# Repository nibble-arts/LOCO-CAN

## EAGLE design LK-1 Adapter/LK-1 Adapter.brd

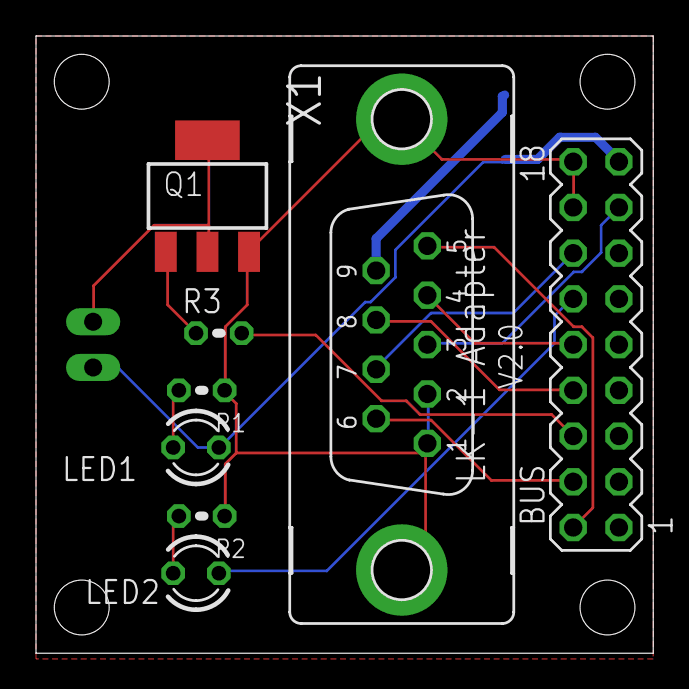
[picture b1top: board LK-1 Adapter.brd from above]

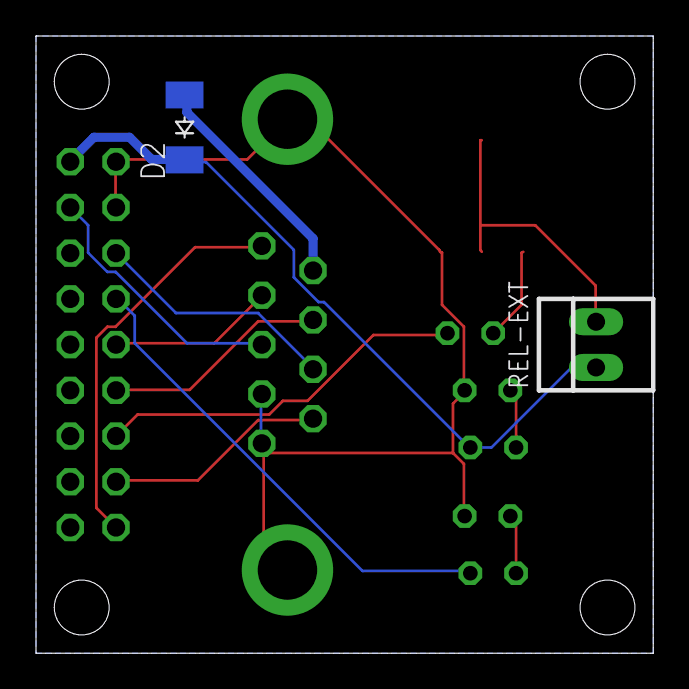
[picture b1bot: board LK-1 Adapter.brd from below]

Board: 2 copper layers, 34.3 x 34.3 mm, 10 parts (2 on the bottom side), 15 nets.

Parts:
BUS: MA09-2
D2: CGRM4004-G; SOD-123_MINI-SMA
LED1, LED2: LED3MM
Q1: N-HEXFET-2D_SOT232-; SOT223
R1: 1K; 0204V
R2: 330R; 0204V
R3: 10K; 0204V
REL-EXT: 22-23-2021
X1: F09VP

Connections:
+12V: BUS.17, D2.C, LED1.A, REL-EXT.1
D2: BUS.2, X1.5
D3: BUS.4, X1.6
D4: BUS.6, R3.2
D5: BUS.8, X1.8
D6: BUS.10, X1.4
D7: BUS.12, LED2.A
D8: BUS.14, X1.7
D9: BUS.15, X1.3
GND: BUS.16, BUS.18, Q1.3, R1.1, R2.1, X1.1, X1.2, X1.G1, X1.G2
unnamed: Q1.1, R3.1
unnamed: Q1.2, Q1.4, REL-EXT.2
unnamed: D2.A, X1.9
unnamed: LED1.K, R1.2
unnamed: LED2.K, R2.2

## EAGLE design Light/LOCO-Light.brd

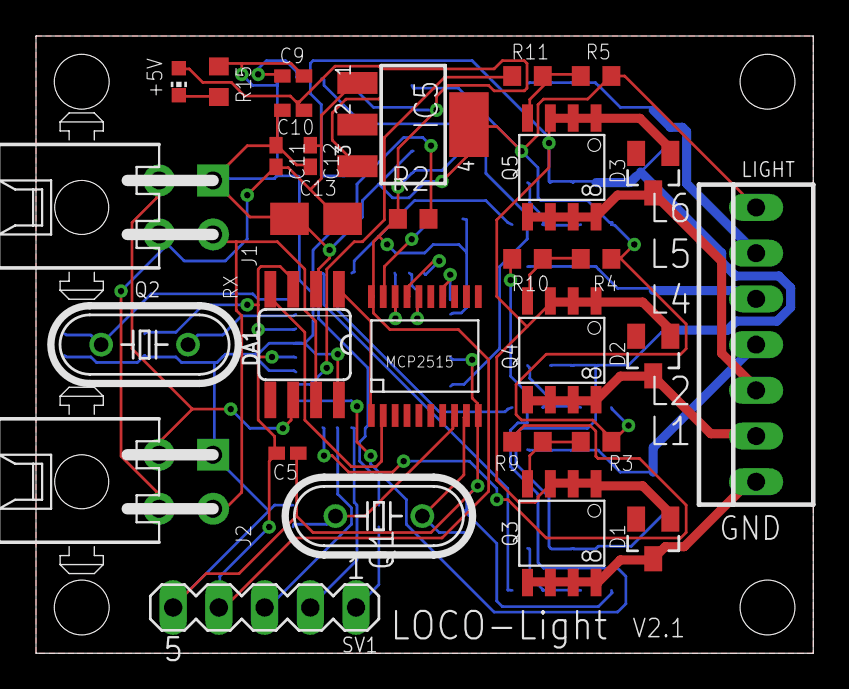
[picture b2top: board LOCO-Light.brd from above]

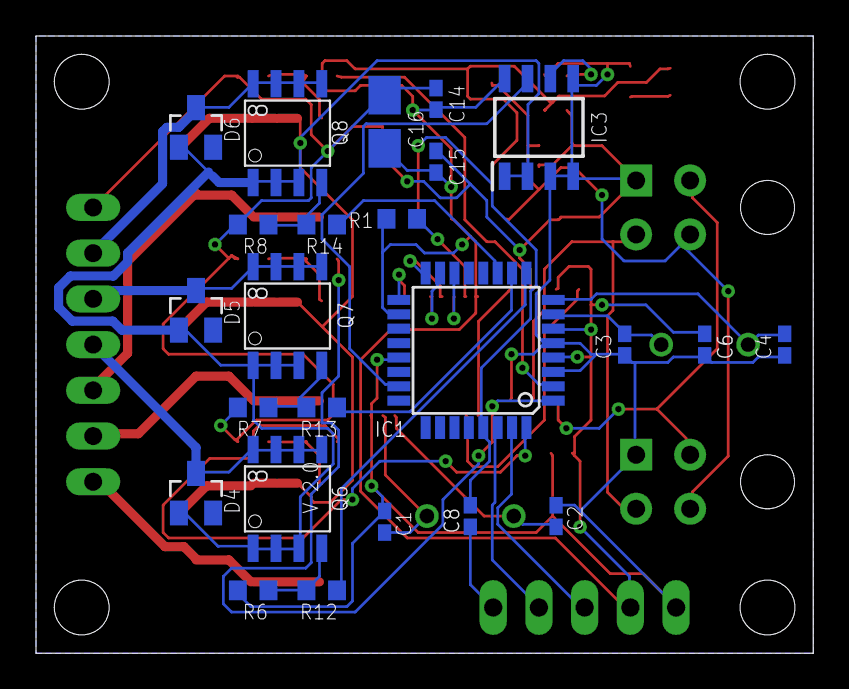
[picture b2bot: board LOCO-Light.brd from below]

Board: 2 copper layers, 43.2 x 34.3 mm, 54 parts (24 on the bottom side), 42 nets.

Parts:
+5V: CHIP-LED0603
C1, C2, C3, C4: 22p; C0402K
C5, C6, C8, C10, C11, C15: 100n; C0402K
C9, C12, C14: 1n; C0402K
C13, C16: 16uF; A/3216-18W
D1, D2, D3, D4, D5, D6: BAS40; SOT23
DA1: TJA1050; SO08
IC1: Atmega 328-P; TQFP32-08
IC2: MCP2515; TSSOP20
IC3: ACS712ELCTR-20A-T; SOIC127P600X175-8N
IC5: LM340MP-05; SOT223
J1, J2: 3-794618-4; SHDRRA4W102P300_2X2_686X892X73
LIGHT: 22-23-2071
Q1: 8MHz; HC49/S
Q2: 16MHz; HC49/S
Q3, Q4, Q5, Q6, Q7, Q8: FDS5680; SO-8
R1, R2, R3, R4, R5, R6, R7, R8, R9, R10, R11, R12, R13, R14, R15: 10k; R0603
SV1: MA05-1

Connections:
+12V: C11.2, C12.2, C13.+, IC5.1, J1.4, J2.4
A0: IC1.23, IC3.7
CAN-H: DA1.7, J1.3, J2.3
CAN-L: DA1.6, J1.2, J2.2
CAN-OCC1: C1.1, IC2.9, Q1.1
CAN-OCC2: C2.1, IC2.8, Q1.2
CS: IC1.14, IC2.18
D2: IC1.32, R9.2
D3: IC1.1, R10.2
D4: IC1.2, R11.2
D5: IC1.9, R12.2
D6: IC1.10, R13.2
D7: IC1.11, R14.2
DTR: C8.1, SV1.1
GND: C1.2, C2.2, C3.2, C4.2, C5.1, C6.2, C9.1, C10.1, C11.1, C12.1, C13.-, C14.1, C15.1, C16.-, DA1.2, DA1.8, IC1.3, IC1.5, IC1.21, IC2.10, IC3.3, IC3.4, IC3.5, IC5.4, J1.1, J2.1, LIGHT.7, R3.1, R4.1, R5.1, R6.1, R7.1, R8.1, R15.1, SV1.5
L1: D1.3, LIGHT.1, Q3.5, Q3.6, Q3.7, Q3.8
L2: D2.3, LIGHT.2, Q4.5, Q4.6, Q4.7, Q4.8
L3: D3.3, LIGHT.3, Q5.5, Q5.6, Q5.7, Q5.8
L4: D4.3, LIGHT.4, Q6.5, Q6.6, Q6.7, Q6.8
L5: D5.3, LIGHT.5, Q7.5, Q7.6, Q7.7, Q7.8
L6: D6.3, LIGHT.6, Q8.5, Q8.6, Q8.7, Q8.8
LIGHT-GND: D1.1, D2.1, D3.1, D4.1, D5.1, D6.1, IC3.1, IC3.2, Q3.1, Q3.2, Q3.3, Q4.1, Q4.2, Q4.3, Q5.1, Q5.2, Q5.3, Q6.1, Q6.2, Q6.3, Q7.1, Q7.2, Q7.3, Q8.1, Q8.2, Q8.3
unnamed: C9.2, IC3.6
unnamed: Q3.4, R3.2, R9.1
unnamed: Q4.4, R4.2, R10.1
unnamed: Q5.4, R5.2, R11.1
unnamed: Q6.4, R6.2, R12.1
unnamed: IC2.19, R1.1
unnamed: Q7.4, R7.2, R13.1
unnamed: Q8.4, R8.2, R14.1
unnamed: C3.1, IC1.7, Q2.1
unnamed: C4.1, IC1.8, Q2.2
unnamed: +5V.C, R15.2
unnamed: C8.2, IC1.29, R2.1
RX: IC1.31, SV1.3
RXCAN: DA1.4, IC2.2
SCK: IC1.17, IC2.14
SI: IC1.16, IC2.17
SO: IC1.15, IC2.16
TX: IC1.30, SV1.2
TXCAN: DA1.1, IC2.1
VCC: +5V.A, C5.2, C6.1, C10.2, C14.2, C15.2, C16.+, DA1.3, IC1.4, IC1.6, IC1.18, IC2.20, IC3.8, IC5.3, R1.2, R2.2, SV1.4

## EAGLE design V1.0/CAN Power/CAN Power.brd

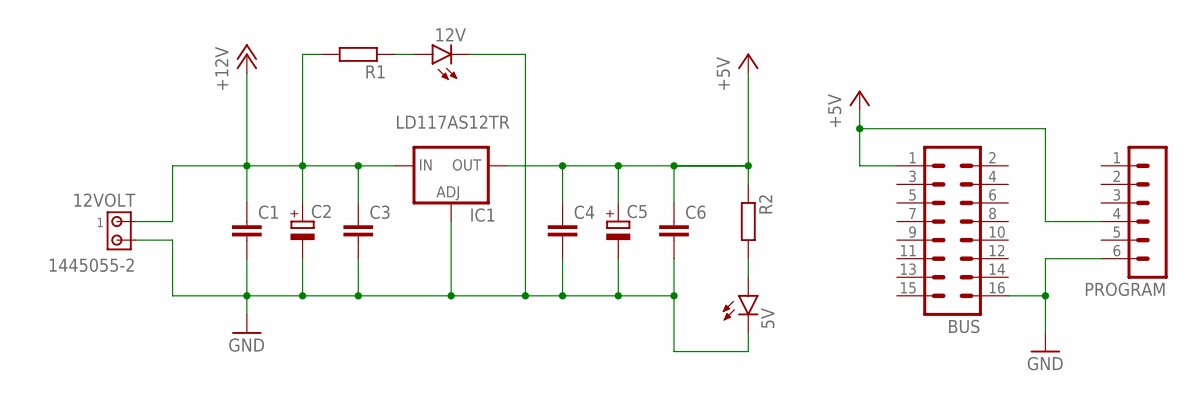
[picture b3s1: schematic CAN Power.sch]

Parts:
5V, 12V: LED3MM
12VOLT: 1445055-2
BUS: MA08-2
C1, C3, C4, C6: C-EUC0402; C0402
C2, C5: CPOL-EUC/6032-28R; C/6032-28R
IC1: LD117AS12TR; SOT223
PROGRAM: MA06-1
R1, R2: R-EU_R0402; R0402

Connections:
+5V: BUS.1, C4.1, C5.+, C6.1, IC1.4 (OUT), PROGRAM.4, R2.1
+12V: 12VOLT.1, C1.1, C2.+, C3.1, IC1.3 (IN), R1.2
GND: 5V.K (C), 12V.K (C), 12VOLT.2, BUS.16, C1.2, C2.-, C3.2, C4.2, C5.-, C6.2, IC1.1 (ADJ), PROGRAM.6
unnamed: 5V.A, R2.2
unnamed: 12V.A, R1.1

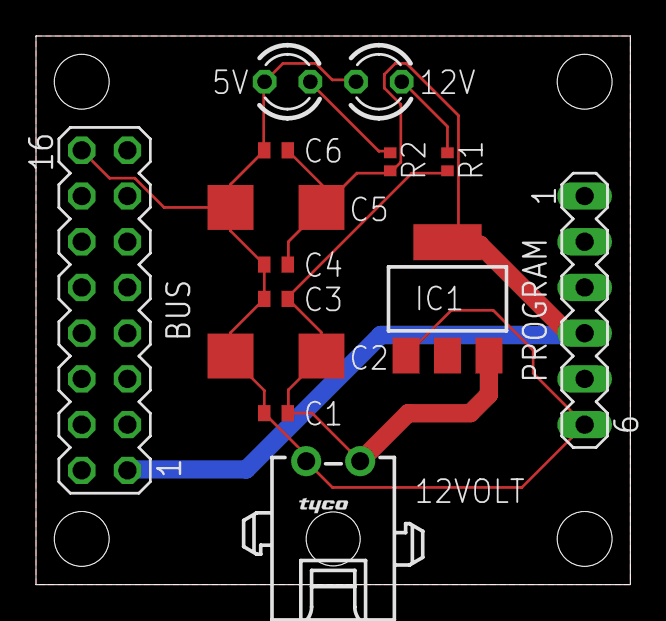
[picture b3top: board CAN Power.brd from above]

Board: 2 copper layers, 33.0 x 30.5 mm, 14 parts (0 on the bottom side), 5 nets.

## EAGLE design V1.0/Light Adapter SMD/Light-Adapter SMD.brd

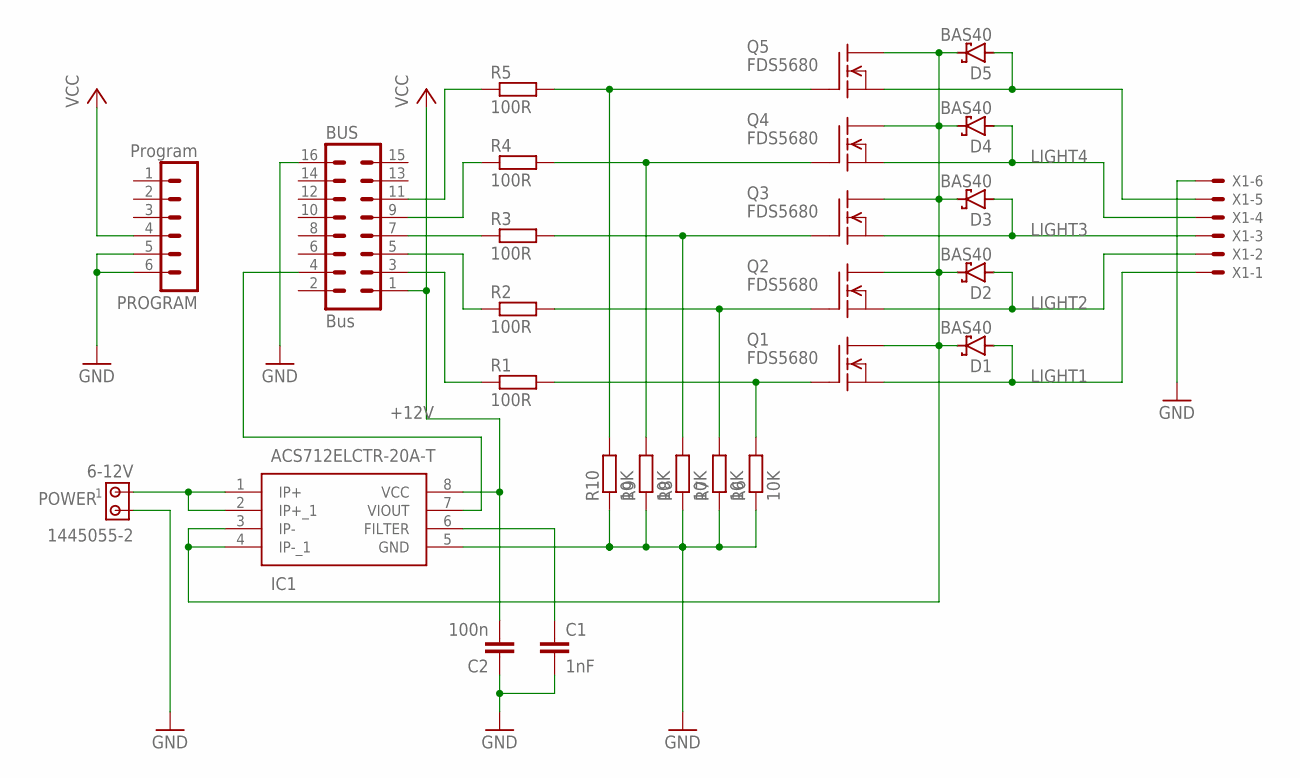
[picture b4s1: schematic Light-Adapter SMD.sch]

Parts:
6-12V: 1445055-2
BUS: Bus; MA08-2
C1: 1nF; C0402
C2: 100n; C0402
D1, D2, D3, D4, D5: BAS40; SOT23
IC1: ACS712ELCTR-20A-T; SOIC127P600X175-8N
PROGRAM: Program; MA06-1
Q1, Q2, Q3, Q4, Q5: FDS5680; SO-8
R1, R2, R3, R4, R5: 100R; R0402
R6, R7, R8, R9, R10: 10K; R0402
X1: 22-23-2061

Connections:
+12V: D1.3 (C), D2.3 (C), D3.3 (C), D4.3 (C), D5.3 (C), IC1.3 (IP-), IC1.4 (IP-_1), Q1.5 (D), Q1.6 (D), Q1.7 (D), Q1.8 (D), Q2.5 (D), Q2.6 (D), Q2.7 (D), Q2.8 (D), Q3.5 (D), Q3.6 (D), Q3.7 (D), Q3.8 (D), Q4.5 (D), Q4.6 (D), Q4.7 (D), Q4.8 (D), Q5.5 (D), Q5.6 (D), Q5.7 (D), Q5.8 (D)
GND: 6-12V.2, BUS.16, C1.2, C2.1, IC1.5 (GND), PROGRAM.5, PROGRAM.6, R6.1, R7.1, R8.1, R9.1, R10.1, X1.6
LIGHT1: D1.1 (A), Q1.1 (S), Q1.2 (S), Q1.3 (S), X1.1
LIGHT2: D2.1 (A), Q2.1 (S), Q2.2 (S), Q2.3 (S), X1.2
LIGHT3: D3.1 (A), Q3.1 (S), Q3.2 (S), Q3.3 (S), X1.3
LIGHT4: D4.1 (A), Q4.1 (S), Q4.2 (S), Q4.3 (S), X1.4
LIGHT5: D5.1 (A), Q5.1 (S), Q5.2 (S), Q5.3 (S), X1.5
unnamed: BUS.3, R1.1
unnamed: BUS.5, R2.1
unnamed: BUS.7, R3.1
unnamed: BUS.9, R4.1
unnamed: BUS.4, IC1.7 (VIOUT)
unnamed: C1.1, IC1.6 (FILTER)
unnamed: BUS.11, R5.1
unnamed: Q5.4 (G), R5.2, R10.2
unnamed: Q4.4 (G), R4.2, R9.2
unnamed: Q3.4 (G), R3.2, R8.2
unnamed: Q2.4 (G), R2.2, R7.2
unnamed: Q1.4 (G), R1.2, R6.2
POWER: 6-12V.1, IC1.1 (IP+), IC1.2 (IP+_1)
VCC: BUS.1, C2.2, IC1.8 (VCC), PROGRAM.4

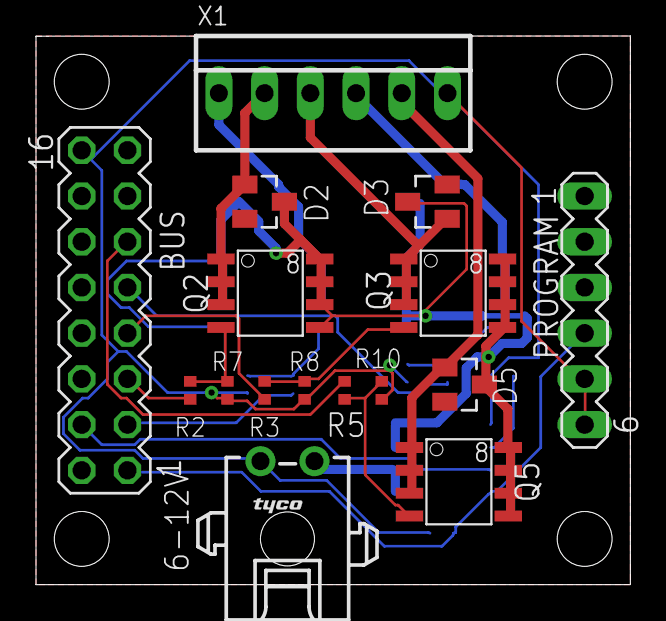
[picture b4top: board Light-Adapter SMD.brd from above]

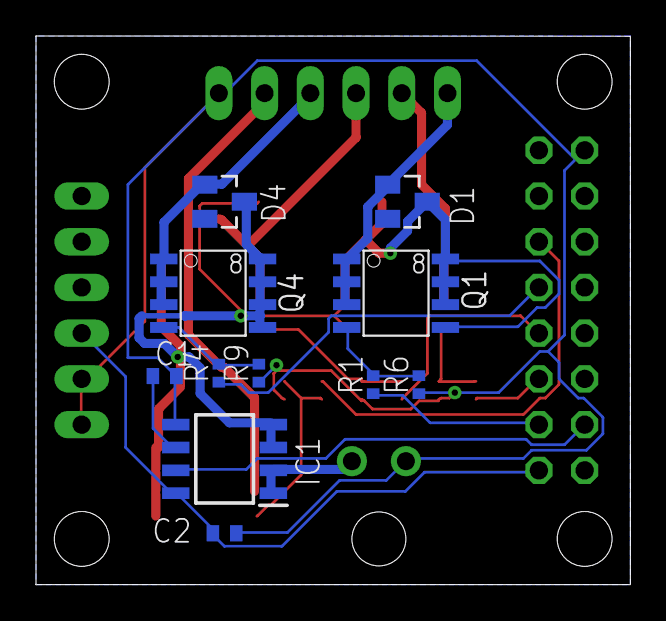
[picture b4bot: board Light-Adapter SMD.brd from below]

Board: 2 copper layers, 33.0 x 30.5 mm, 27 parts (11 on the bottom side), 21 nets.

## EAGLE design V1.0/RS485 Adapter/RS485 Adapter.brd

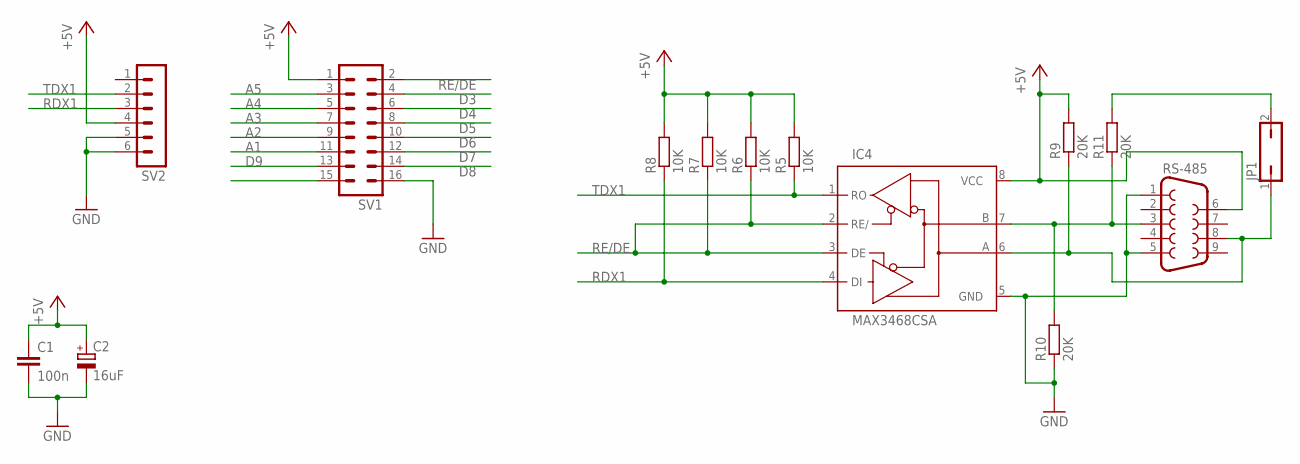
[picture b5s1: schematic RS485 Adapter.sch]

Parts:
C1: 100n; C0402
C2: 16uF; A/3216-18R
IC4: MAX3468CSA; SO08
JP1: JP1Q; JP1
R5, R6, R7, R8: 10K; MINI_MELF-0102R
R9, R10, R11: 20K; MINI_MELF-0102R
RS-485: F09V
SV1: MA08-2
SV2: MA06-1

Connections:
+5V: C1.1, C2.+, IC4.8 (VCC), R5.2, R6.2, R7.2, R8.2, R9.2, RS-485.6, SV1.1, SV2.4
A1: SV1.11
A2: SV1.9
A3: SV1.7
A4: SV1.5
A5: SV1.3
D3: SV1.4
D4: SV1.6
D5: SV1.8
D6: SV1.10
D7: SV1.12
D8: SV1.14
D9: SV1.13
GND: C1.2, C2.-, IC4.5 (GND), R10.1, RS-485.1, RS-485.5, SV1.16, SV2.5, SV2.6
IO14: SV1.15
unnamed: IC4.6 (A), JP1.1, R9.1, RS-485.8
unnamed: IC4.7 (B), R10.2, R11.1, RS-485.3
unnamed: JP1.2, R11.2
RDX1: IC4.4 (DI), R8.1, SV2.3
RE/DE: IC4.2 (RE/), IC4.3 (DE), R6.1, R7.1, SV1.2
TDX1: IC4.1 (RO), R5.1, SV2.2

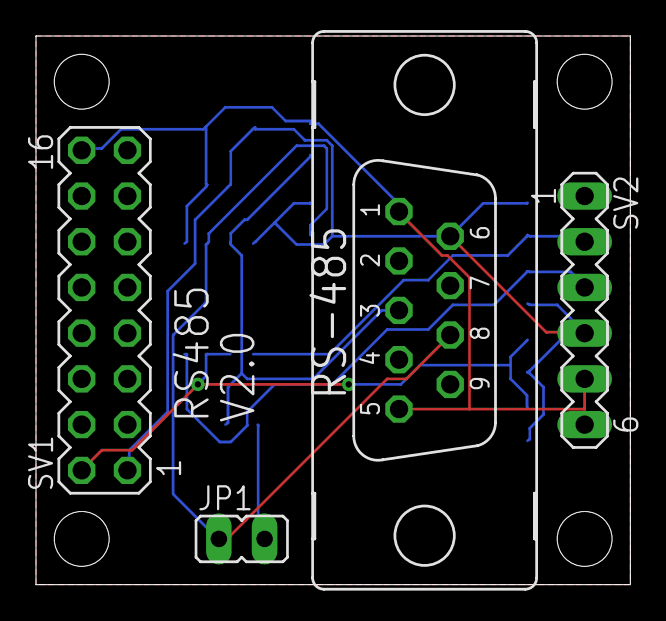
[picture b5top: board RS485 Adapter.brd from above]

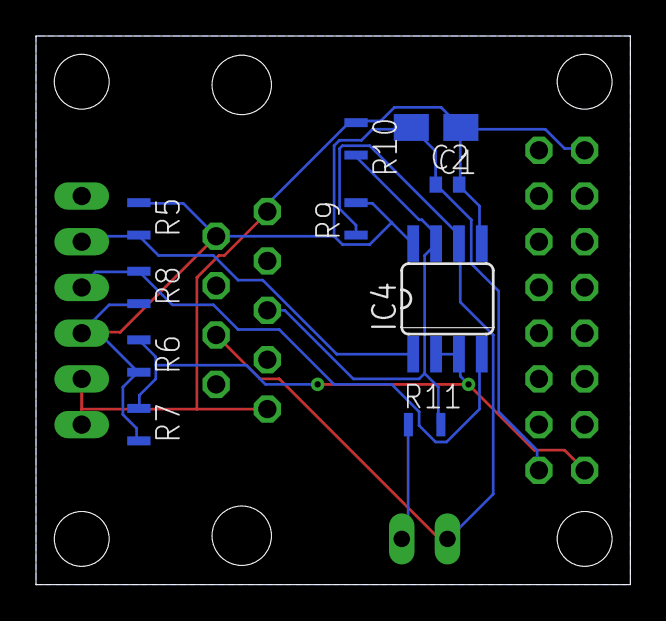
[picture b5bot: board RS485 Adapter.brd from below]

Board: 2 copper layers, 33.0 x 30.5 mm, 14 parts (10 on the bottom side), 8 nets.

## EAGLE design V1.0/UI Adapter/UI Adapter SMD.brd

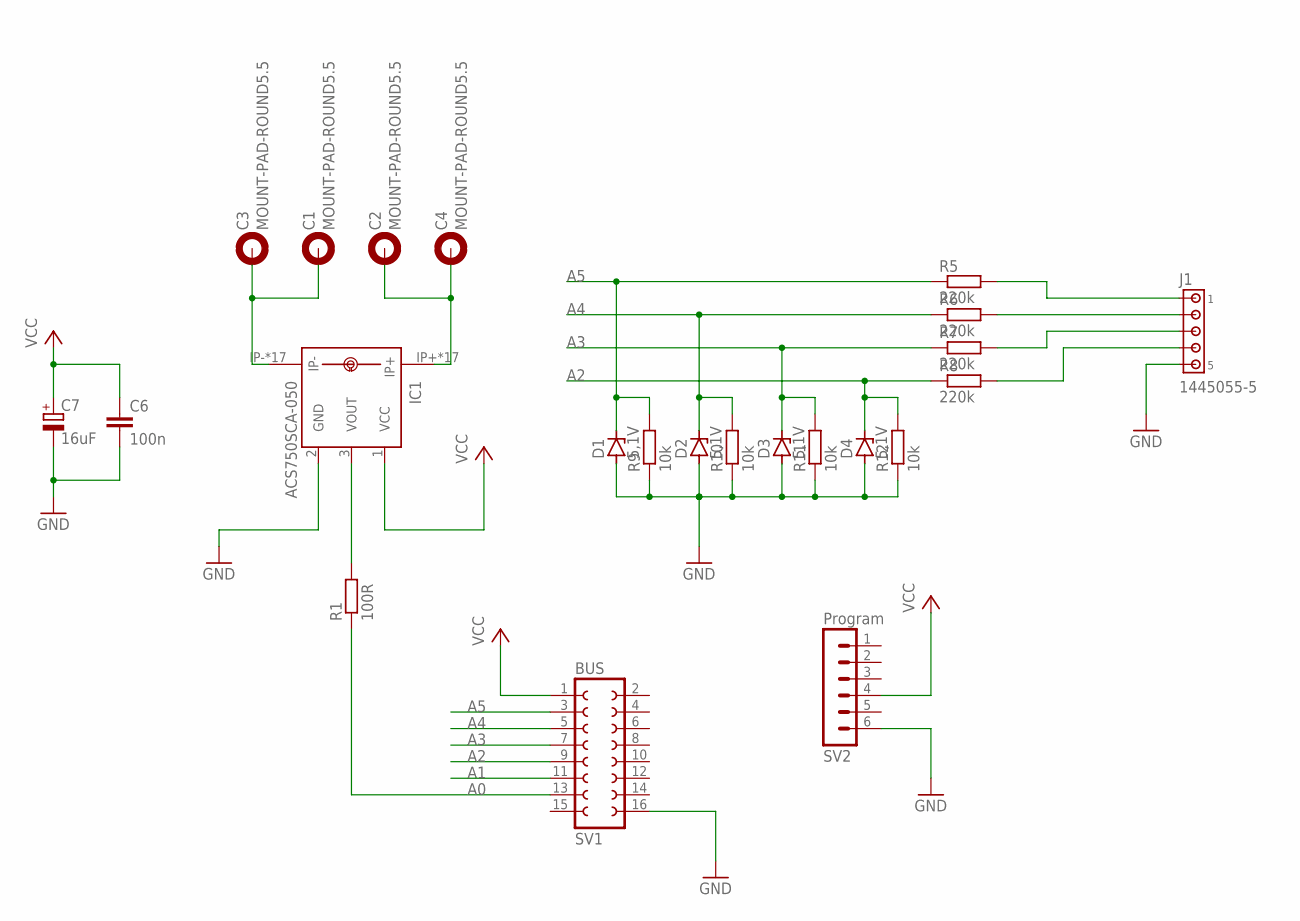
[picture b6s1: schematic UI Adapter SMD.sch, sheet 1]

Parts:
C1, C2, C3, C4: MOUNT-PAD-ROUND5.5; 5,5-PAD
C6: 100n; C0402K
C7: 16uF; A/3216-18W
D1, D2, D3, D4: 5,1V; SOD80C
IC1: ACS750SCA-050; ACS75050
J1: 1445055-5
R1: 100R; R0402
R5, R6, R7, R8: 220k; R0402
R9, R10, R11, R12: 10k; R0402
SV1: BUS; FE08-2
SV2: Program; MA06-1

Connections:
A0: R1.1, SV1.13
A1: SV1.11
A2: D4.C, R8.1, R12.2, SV1.9
A3: D3.C, R7.1, R11.2, SV1.7
A4: D2.C, R6.1, R10.2, SV1.5
A5: D1.C, R5.1, R9.2, SV1.3
C1: C1.B5,5, C3.B5,5, IC1.IP-, IC1.IP-@2 (IP-), IC1.IP-@3 (IP-), IC1.IP-@4 (IP-), IC1.IP-@5 (IP-), IC1.IP-@6 (IP-), IC1.IP-@7 (IP-), IC1.IP-@8 (IP-), IC1.IP-@9 (IP-), IC1.IP-@10 (IP-), IC1.IP-@11 (IP-), IC1.IP-@12 (IP-), IC1.IP-@13 (IP-), IC1.IP-@14 (IP-), IC1.IP-@15 (IP-), IC1.IP-@16 (IP-), IC1.IP-@17 (IP-)
C2: C2.B5,5, C4.B5,5, IC1.IP+, IC1.IP+@2 (IP+), IC1.IP+@3 (IP+), IC1.IP+@4 (IP+), IC1.IP+@5 (IP+), IC1.IP+@6 (IP+), IC1.IP+@7 (IP+), IC1.IP+@8 (IP+), IC1.IP+@9 (IP+), IC1.IP+@10 (IP+), IC1.IP+@11 (IP+), IC1.IP+@12 (IP+), IC1.IP+@13 (IP+), IC1.IP+@14 (IP+), IC1.IP+@15 (IP+), IC1.IP+@16 (IP+), IC1.IP+@17 (IP+)
GND: C6.2, C7.-, D1.A, D2.A, D3.A, D4.A, IC1.2 (GND), J1.5, R9.1, R10.1, R11.1, R12.1, SV1.16, SV2.6
unnamed: IC1.3 (VOUT), R1.2
unnamed: J1.1, R5.2
unnamed: J1.2, R6.2
unnamed: J1.3, R7.2
unnamed: J1.4, R8.2
VCC: C6.1, C7.+, IC1.1 (VCC), SV1.1, SV2.4

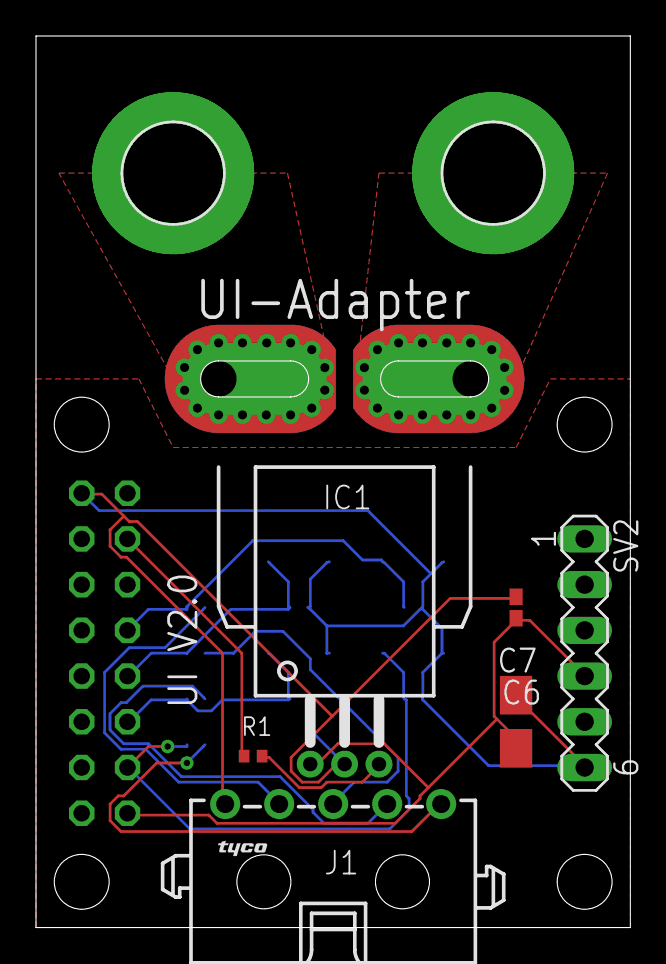
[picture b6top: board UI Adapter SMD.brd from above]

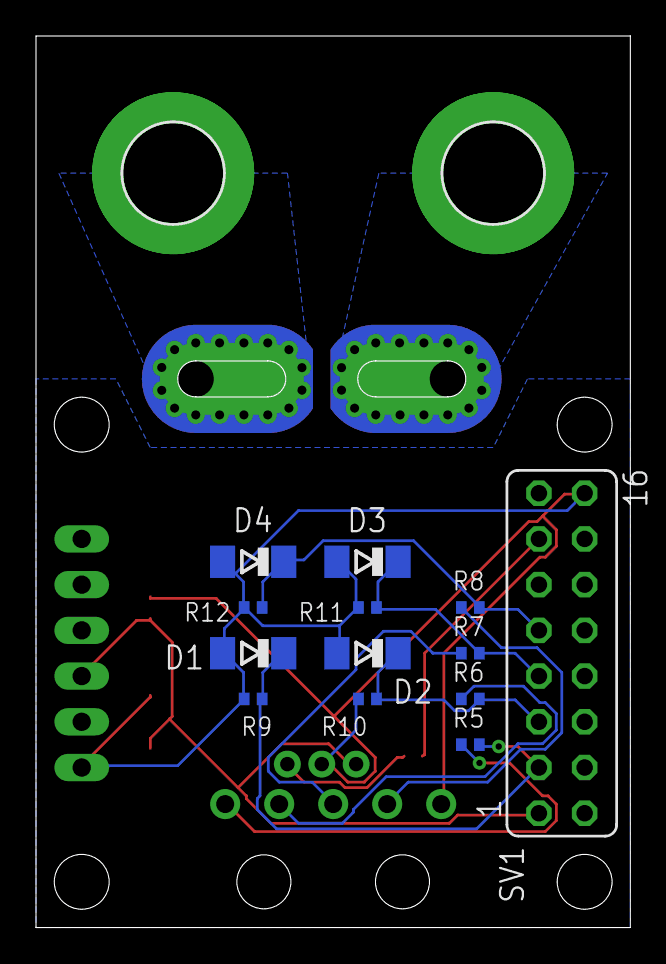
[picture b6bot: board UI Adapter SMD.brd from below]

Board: 2 copper layers, 33.0 x 49.5 mm, 23 parts (15 on the bottom side), 14 nets.

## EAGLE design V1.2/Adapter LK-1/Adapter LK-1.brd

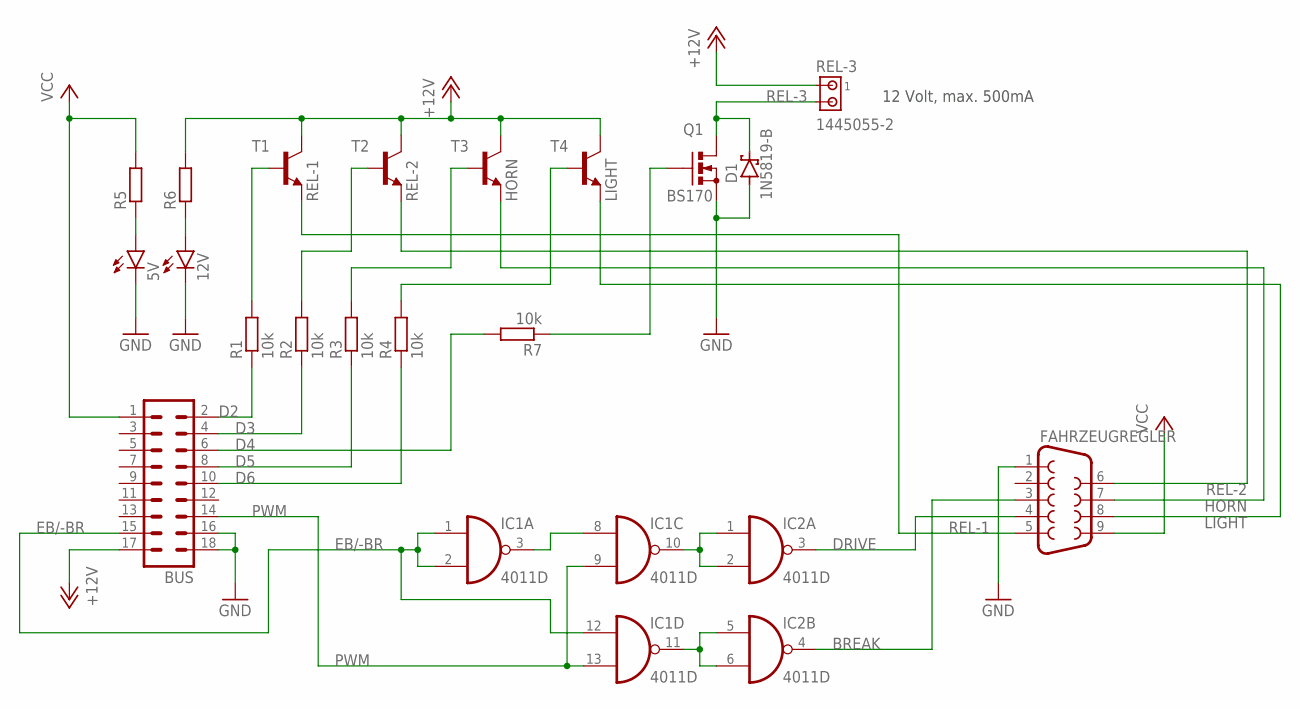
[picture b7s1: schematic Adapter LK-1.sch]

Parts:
5V, 12V: LED3MM
BUS: MA09-2
D1: 1N5819-B; DO41-7.6
FAHRZEUGREGLER: F09HP
IC1, IC2: 4011D; SO14
Q1: BS170; SOT54E
R1, R2, R3, R4, R7: 10k; 0204V
R5, R6: R-EU_0204/2V; 0204V
REL-3: 1445055-2
T1, T2, T3, T4: -NPN-TO92; TO92

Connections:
+12V: BUS.17, R6.2, REL-3.1, T1.3 (C), T2.3 (C), T3.3 (C), T4.3 (C)
BREAK: FAHRZEUGREGLER.3, IC2.4 (O)
D2: BUS.2, R1.1
D3: BUS.4, R2.1
D4: BUS.6, R7.2
D5: BUS.8, R3.1
D6: BUS.10, R4.1
DRIVE: FAHRZEUGREGLER.4, IC2.3 (O)
EB/-BR: BUS.15, IC1.1 (I0), IC1.2 (I1), IC1.12 (I0)
GND: 5V.K (C), 12V.K (C), BUS.16, BUS.18, D1.A, FAHRZEUGREGLER.1, Q1.S
HORN: FAHRZEUGREGLER.7, T3.1 (E)
LIGHT: FAHRZEUGREGLER.8, T4.1 (E)
unnamed: IC1.3 (O), IC1.8 (I0)
unnamed: R1.2, T1.2 (B)
unnamed: R2.2, T2.2 (B)
unnamed: IC1.10 (O), IC2.1 (I0), IC2.2 (I1)
unnamed: IC1.11 (O), IC2.5 (I0), IC2.6 (I1)
unnamed: R3.2, T3.2 (B)
unnamed: R4.2, T4.2 (B)
unnamed: 5V.A, R5.1
unnamed: 12V.A, R6.1
unnamed: Q1.G, R7.1
PWM: BUS.14, IC1.9 (I1), IC1.13 (I1)
REL-1: FAHRZEUGREGLER.5, T1.1 (E)
REL-2: FAHRZEUGREGLER.6, T2.1 (E)
REL-3: D1.C, Q1.D, REL-3.2
VCC: BUS.1, FAHRZEUGREGLER.9, R5.2
VDD: IC1.14 (VDD), IC2.14 (VDD)
VSS: IC1.7 (VSS), IC2.7 (VSS)

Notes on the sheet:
12 Volt, max. 500mA

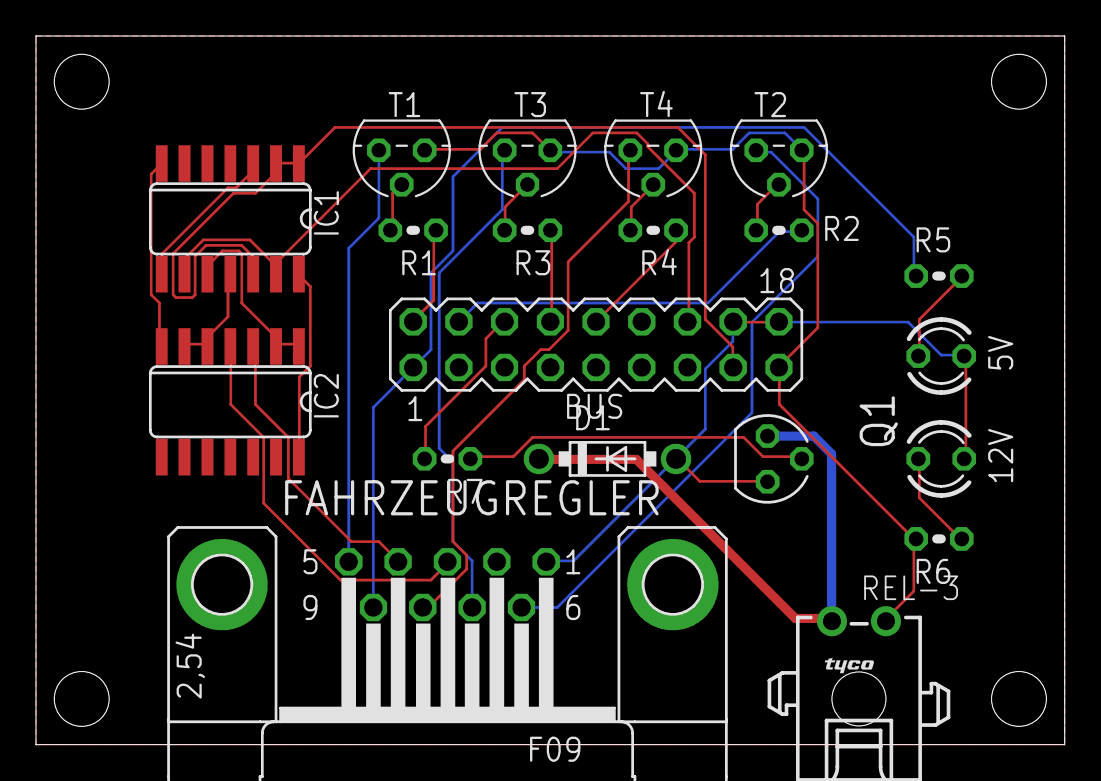
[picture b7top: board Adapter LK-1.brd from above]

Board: 2 copper layers, 57.1 x 39.4 mm, 20 parts (0 on the bottom side), 29 nets.
